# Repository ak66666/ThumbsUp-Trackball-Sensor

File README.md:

# PMW3360 breakout board

# A clone of https://github.com/jfedor2/pmw3360-breakout

Changes inlclude:
- Layout modified to make the board narrower.
- Connector for a 12 line flexible cable replaced the pin headers.
The rest is practically the same.

This repository contains PCB design files for a breakout board for the PMW3360 optical mouse sensor.

The board doesn't do any level shifting so it only works with 3.3V logic.

The dimensions of the board are 40mm x 15mm, the mounting holes are for M2 screws.

The files in the [fabrication](fabrication) folder can be used to order this board from JLCPCB with SMT assembly. 
The board you get includes everything except the actual sensor. 
If some of the specific components are out of stock, try to find an equivalent with the same package and parameters.

The sensor chip should be soldered on the top side (the side where all the other components are). 
The dot marks pin 1. The optic goes on the bottom side.

//TODO

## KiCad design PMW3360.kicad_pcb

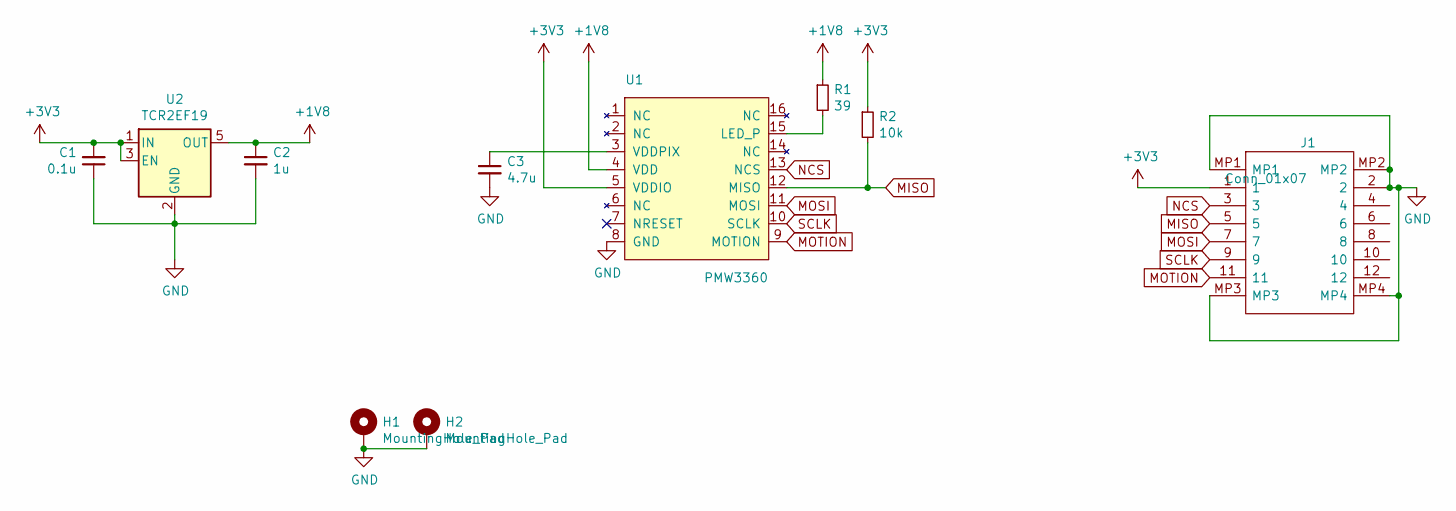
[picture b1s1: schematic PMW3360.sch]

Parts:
C1: 0.1u; C_0603_1608Metric; LCSC C14663
C2: 1u; C_0603_1608Metric; LCSC C15849
C3: 4.7u; C_0603_1608Metric; LCSC C19666
H1, H2: MountingHole_Pad; MountingHole_2.2mm_M2
J1: Conn_01x07; 525591233; Manufacturer_Part_Number 52559-1233; Mouser Part Number 538-52559-1233
R1: 39; R_0603_1608Metric; LCSC C137733
R2: 10k; R_0603_1608Metric; LCSC C25804
U1: PMW3360
U2: TCR2EF19; SOT-23-5; LCSC C146366

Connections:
+1V8: C2.1, R1.1, U1.4 (VDD), U2.5 (OUT)
+3V3: C1.2, J1.1, R2.1, U1.5 (VDDIO), U2.1 (IN), U2.3 (EN)
GND: C1.1, C2.2, C3.2, H1.1, H2.1, J1.2, J1.MP1, J1.MP2, J1.MP3, J1.MP4, U1.8 (GND), U2.2 (GND)
MISO: J1.5, R2.2, U1.12 (MISO)
MOSI: J1.7, U1.11 (MOSI)
MOTION: J1.11, U1.9 (MOTION)
NCS: J1.3, U1.13 (NCS)
unnamed: C3.1, U1.3 (VDDPIX)
unnamed: R1.2, U1.15 (LED_P)
SCLK: J1.9, U1.10 (SCLK)

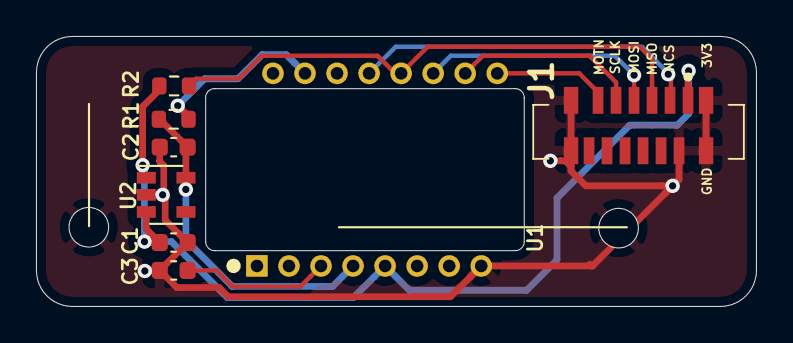
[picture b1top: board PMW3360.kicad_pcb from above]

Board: 2 copper layers, 40.0 x 15.0 mm, 10 parts (0 on the bottom side), 10 nets.

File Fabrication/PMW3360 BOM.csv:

Designator,Footprint,Quantity,Designation,LCSC
U2,SOT-23-5,1,TCR2EF19,
R2,R_0603_1608Metric,1,10k,C25804
R1,R_0603_1608Metric,1,39,C137733
C3,C_0603_1608Metric,1,4.7u,C19666
C2,C_0603_1608Metric,1,1u,C15849
C1,C_0603_1608Metric,1,0.1u,C14663

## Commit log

2025-05-07 Added a PMW3360 breakout board cloned from jfedor2's original design.
2025-05-07 Added board renders.
2025-05-07 Adjusted board edges so it is square and the main measures are rounded.
2025-05-10 Corrected the power lines - connected them to the right pins of the sockets.
